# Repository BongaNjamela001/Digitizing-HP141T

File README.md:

# HP141T Spectrogram Display Project

This repository contains the complete set of files for the HP141T Spectrogram Display project, including hardware designs, simulations, software, and documentation. The project aims to visualize time-domain spectrogram data from the HP141T spectrum analyzer on a touchscreen LCD, replicating the CRT display with a green trace and grid.

## Repository Structure

The repository is organized into the following main folders:

- **PCBs/**: Hardware design files for the HP141T emulator and Signal Conditioning Subsystem.
- **Presentation/**: Materials for project presentations.
- **Report/**: Project report and associated LaTeX files.
- **Results/**: Output data and results from the project.
- **Simulations/**: Simulation files for circuit and signal analysis.
- **Software/**: Python scripts for data processing and GUI implementation.

### PCBs
This folder contains the PCB design files for the project, divided into two subdirectories:

- **HP141T_Emulator/**: KiCad project files and Gerber files for the HP141T emulator PCB.
- **Signal_Conditioning_Subsystem/**: KiCad project files and Gerber files for the Signal Conditioning Subsystem PCB.

### Presentation
This folder includes materials prepared for project presentations:

- **Poster/**: The project poster in PDF format.
- **Oral_Assessment/**: PowerPoint presentation (`.pptx`) for the oral assessment.

### Report
This folder contains the project report and its source files:

- **LaTeX/**: LaTeX source files for the project report.
- **Final_Report/**: Compiled PDF of the final project report.

### Results
This folder stores the output data and results generated during the project. It includes CSV files (e.g., `das-data_01.csv` to `das-data_64.csv`) with time and voltage measurements used for spectrogram visualization.

### Simulations
This folder contains simulation files for circuit and signal analysis:

- **LTSpice/**: LTSpice simulation files for circuit design validation.
- **MATLAB/**: MATLAB scripts and simulation files for signal processing and analysis.

### Software
This folder includes the software developed for the project:

- **DPS/**: Python scripts for data processing (e.g., `spectrogram_display_documented.py`).
- **GUIs/**: Python scripts for graphical user interfaces to interact with the spectrogram display.

## Usage

To explore the repository:

1. **Hardware**: Use KiCad to open the PCB design files in the `PCBs/` folder. Gerber files can be used for manufacturing.
2. **Simulations**: Run LTSpice simulations directly from the `.asc` files, or use MATLAB to execute the signal processing scripts.
3. **Software**: Navigate to the `Software/DPS/` folder to run the Python scripts. Ensure dependencies like `pandas`, `matplotlib`, and `tkinter` are installed. For example:
   ```bash
   python spectrogram_display_documented.py
   ```
4. **Documentation**: View the final report in `Report/Final_Report/` or compile the LaTeX source in `Report/LaTeX/`.

## License

This project is licensed under the MIT License. See the `LICENSE` file for details (to be added).

## Contributing

Contributions are welcome! Please submit a pull request or open an issue to discuss improvements or bug fixes.

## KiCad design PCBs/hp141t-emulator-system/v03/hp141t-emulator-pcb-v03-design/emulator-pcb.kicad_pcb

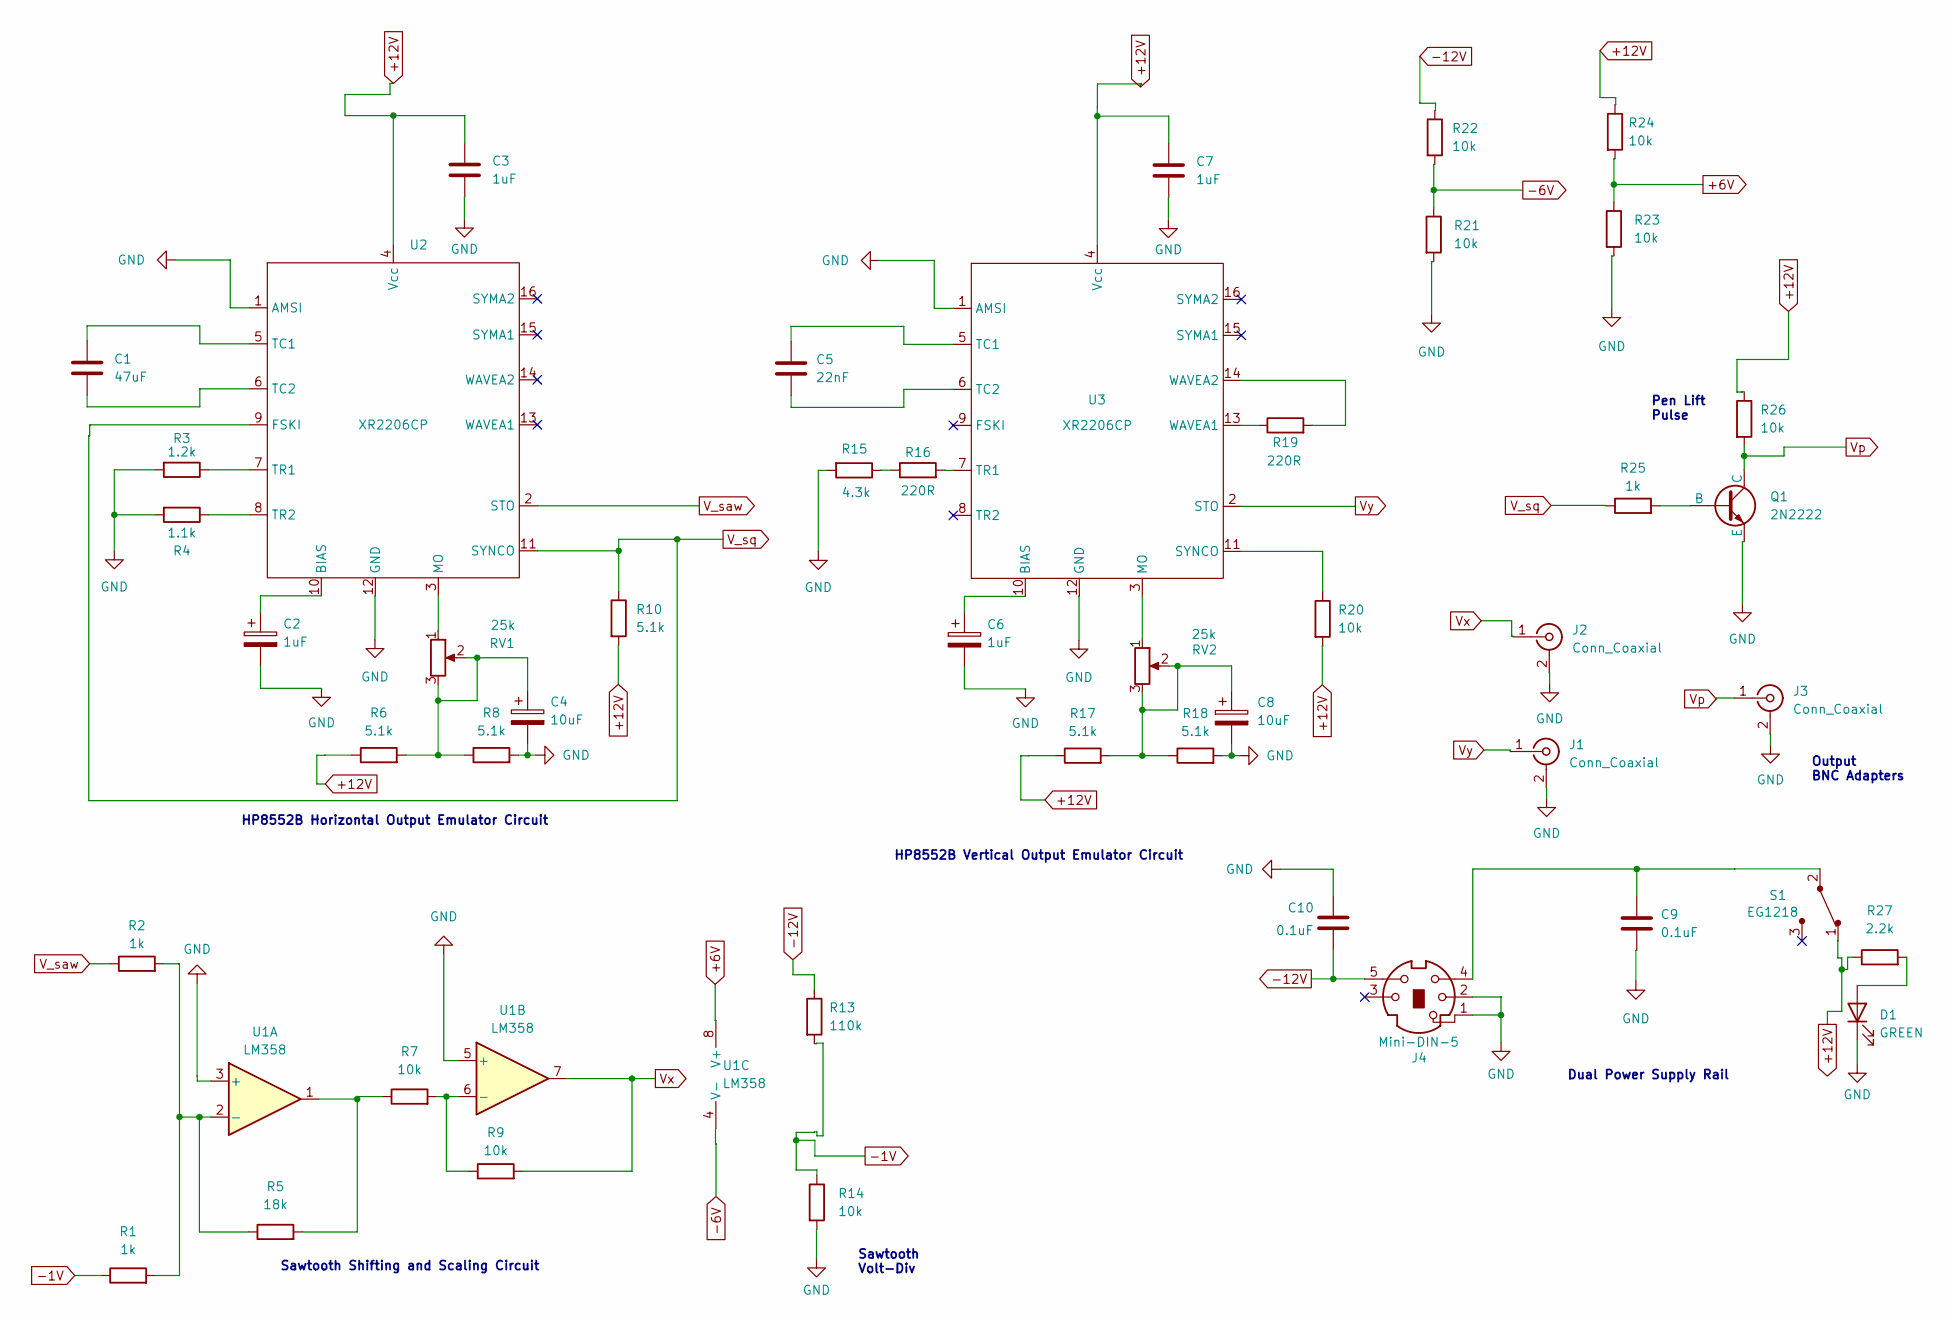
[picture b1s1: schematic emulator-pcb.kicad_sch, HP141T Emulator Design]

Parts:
C1: 47uF; C_Axial_L12.0mm_D6.5mm_P20.00mm_Horizontal
C2, C6: 1uF; CP_Radial_D6.3mm_P2.50mm
C3, C7: 1uF; C_Axial_L3.8mm_D2.6mm_P7.50mm_Horizontal
C4, C8: 10uF; CP_Radial_D4.0mm_P1.50mm
C5: 22nF; C_Axial_L3.8mm_D2.6mm_P7.50mm_Horizontal
C9, C10: 0.1uF; C_Axial_L3.8mm_D2.6mm_P7.50mm_Horizontal
D1: GREEN; LED_D5.0mm
J1, J2, J3: Conn_Coaxial; BNC_Amphenol_B6252HB-NPP3G-50_Horizontal
J4: Mini-DIN-5; PinSocket_DIN41524_1x05_P2.54mm_Vertical
Q1: 2N2222; TO-92_Inline
R1, R2, R25: 1k; R_Axial_DIN0207_L6.3mm_D2.5mm_P7.62mm_Horizontal
R3: 1.2k; R_Axial_DIN0207_L6.3mm_D2.5mm_P7.62mm_Horizontal
R4: 1.1k; R_Axial_DIN0207_L6.3mm_D2.5mm_P7.62mm_Horizontal
R5: 18k; R_Axial_DIN0207_L6.3mm_D2.5mm_P7.62mm_Horizontal
R6, R8, R10, R17, R18: 5.1k; R_Axial_DIN0207_L6.3mm_D2.5mm_P7.62mm_Horizontal
R7, R9, R14, R20, R21, R22, R23, R24, R26: 10k; R_Axial_DIN0207_L6.3mm_D2.5mm_P7.62mm_Horizontal
R13: 110k; R_Axial_DIN0207_L6.3mm_D2.5mm_P7.62mm_Horizontal
R15: 4.3k; R_Axial_DIN0207_L6.3mm_D2.5mm_P7.62mm_Horizontal
R16, R19: 220R; R_Axial_DIN0207_L6.3mm_D2.5mm_P7.62mm_Horizontal
R27: 2.2k; R_Axial_DIN0207_L6.3mm_D2.5mm_P7.62mm_Horizontal
RV1, RV2: 25k; BOURNS-3362P_pot
S1: EG1218; Switch_Slide_11.6x4mm_EG1218; MPN EG1218; Digi-Key_PN EG1903-ND
U1: LM358; DIP-8_W7.62mm_Socket
U2, U3: XR2206CP; Socket_DIP-16_7.62mm_Conn

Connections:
+6V: R23.1, R24.2, U1.8 (V+)
+12V: C3.1, C7.1, R6.1, R10.2, R17.1, R20.2, R24.1, R26.1, R27.1, S1.1, U2.4 (Vcc), U3.4 (Vcc)
-1V: R1.1, R13.2, R14.1
-6V: R21.1, R22.2, U1.4 (V-)
-12V: C10.2, J4.5, R13.1, R22.1
GND: C2.2, C3.2, C4.2, C6.2, C7.2, C8.2, C9.2, C10.1, D1.1 (K), J1.2 (Ext), J2.2 (Ext), J3.2 (Ext), J4.1, J4.2, Q1.3 (E), R3.2, R4.2, R8.2, R14.2, R15.2, R18.2, R21.2, R23.2, U1.3 (+), U1.5 (+), U2.1 (AMSI), U2.12 (GND), U3.1 (AMSI), U3.12 (GND); also elsewhere on the board
unnamed: C4.1, R6.2, R8.1, RV1.2, RV1.3
unnamed: C8.1, R17.2, R18.1, RV2.2, RV2.3
unnamed: C9.1, J4.4, S1.2
unnamed: D1.2 (A), R27.2
unnamed: Q1.2 (B), R25.2
unnamed: R5.2, R7.1, U1.1
unnamed: R15.1, R16.1
unnamed: R1.2, R2.2, R5.1, U1.2 (-)
unnamed: R7.2, R9.1, U1.6 (-)
unnamed: C2.1, U2.10 (BIAS)
unnamed: RV1.1, U2.3 (MO)
unnamed: C1.1, U2.5 (TC1)
unnamed: C1.2, U2.6 (TC2)
unnamed: R3.1, U2.7 (TR1)
unnamed: R4.1, U2.8 (TR2)
unnamed: C6.1, U3.10 (BIAS)
unnamed: RV2.1, U3.3 (MO)
unnamed: R20.1, U3.11 (SYNCO)
unnamed: C5.1, U3.5 (TC1)
unnamed: C5.2, U3.6 (TC2)
unnamed: R16.2, U3.7 (TR1)
unnamed: R19.1, U3.13 (WAVEA1)
unnamed: R19.2, U3.14 (WAVEA2)
V_saw: R2.1, U2.2 (STO)
V_sq: R10.1, R25.1, U2.9 (FSKI), U2.11 (SYNCO)
Vp: J3.1 (In), Q1.1 (C), R26.2
Vx: J2.1 (In), R9.2, U1.7
Vy: J1.1 (In), U3.2 (STO)

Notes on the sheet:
Dual Power Supply Rail
Sawtooth Shifting and Scaling Circuit
Output BNC Adapters
Pen Lift Pulse
HP8552B Horizontal Output Emulator Circuit
Sawtooth Volt-Div
HP8552B Vertical Output Emulator Circuit

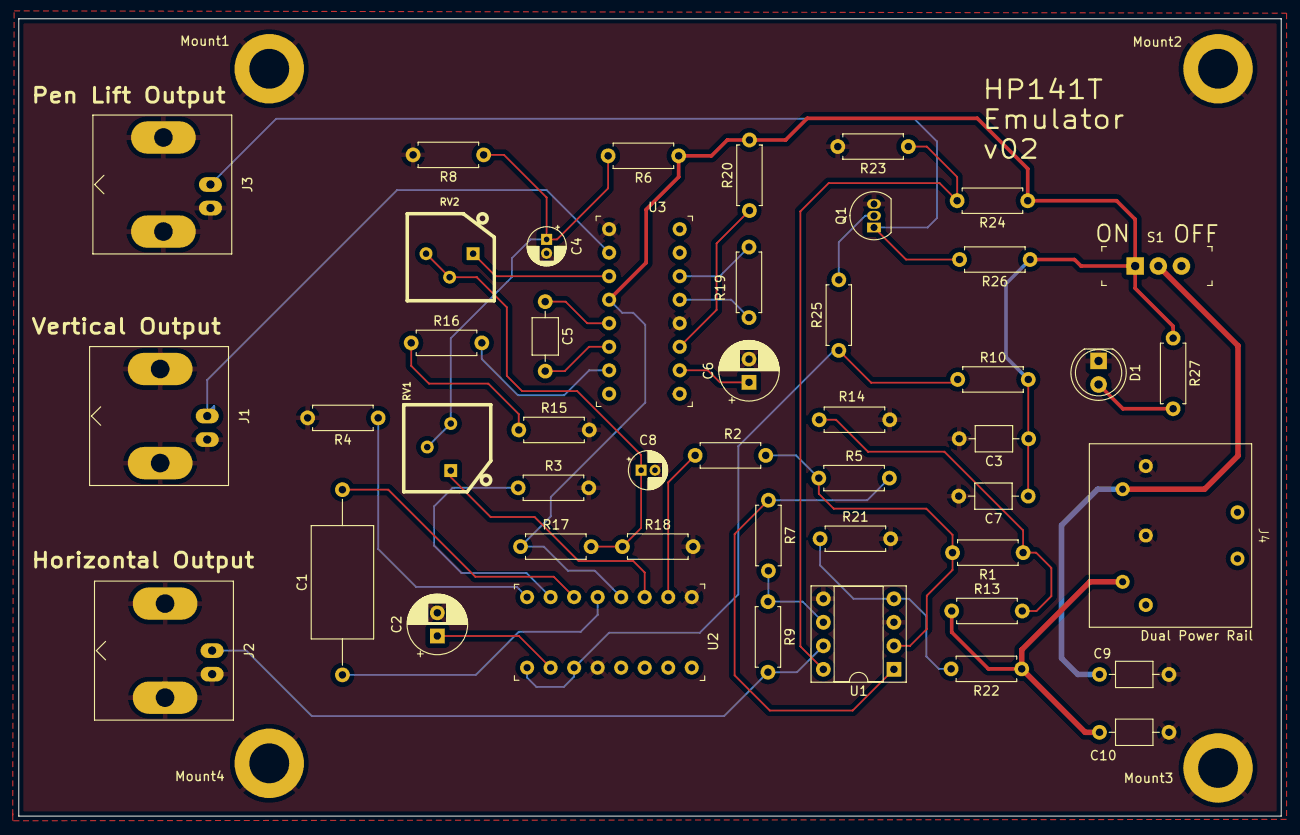
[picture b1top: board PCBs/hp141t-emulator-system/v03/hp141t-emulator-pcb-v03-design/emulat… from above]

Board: 2 copper layers, 136.3 x 86.1 mm, 51 parts (0 on the bottom side), 34 nets.

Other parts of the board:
Mount1, Mount2, Mount3, Mount4: MountingHole_4.3mm_M4_DIN965_Pad

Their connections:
GND: Mount1.1, Mount2.1, Mount3.1, Mount4.1; also elsewhere on the board

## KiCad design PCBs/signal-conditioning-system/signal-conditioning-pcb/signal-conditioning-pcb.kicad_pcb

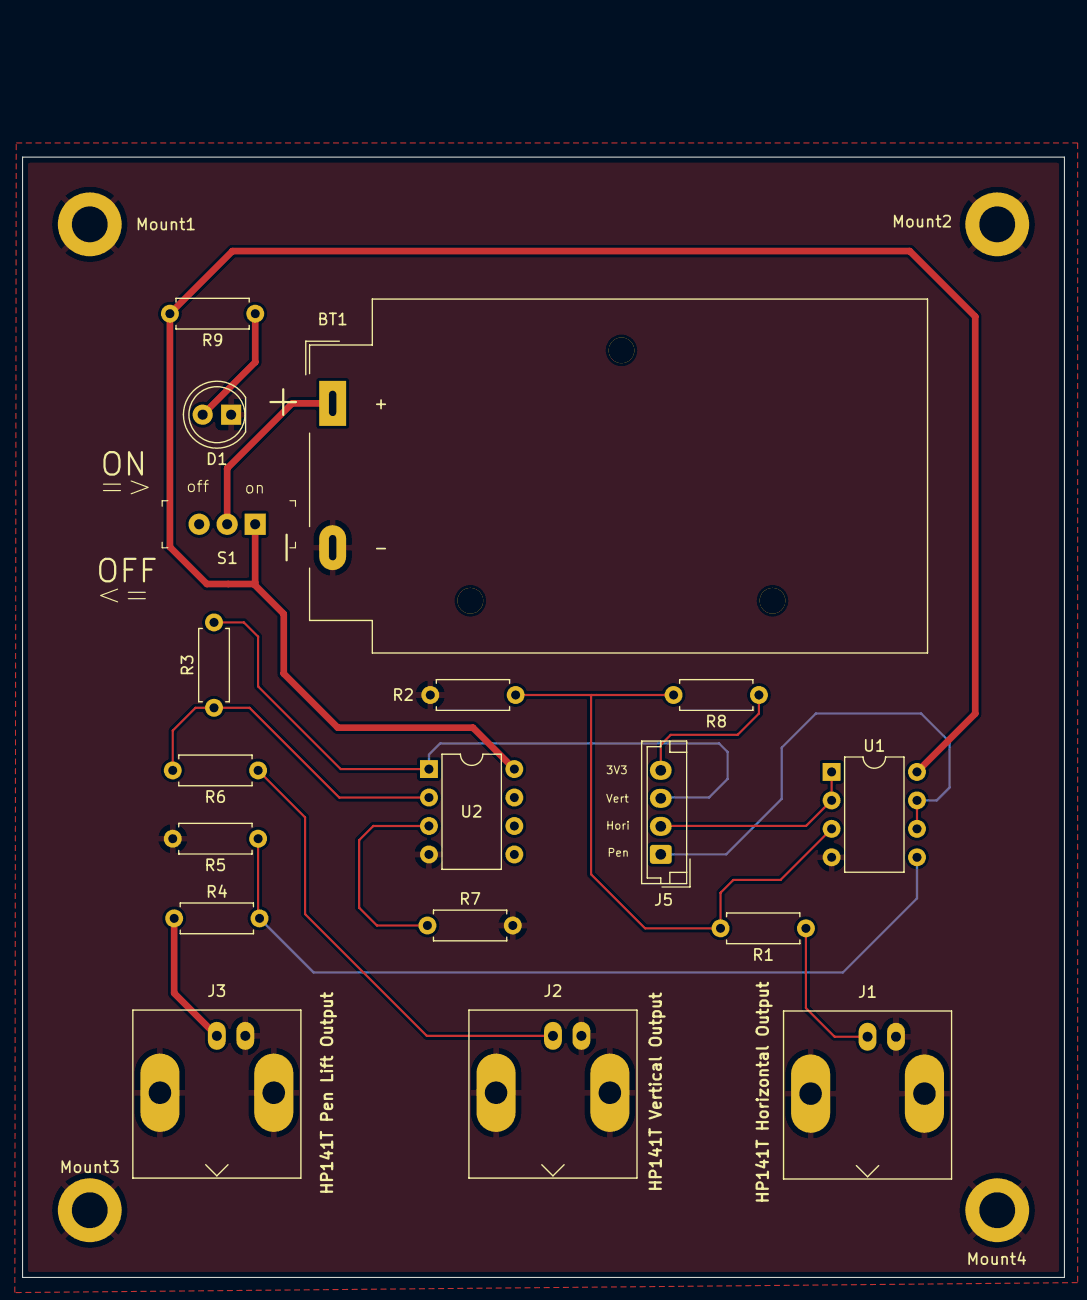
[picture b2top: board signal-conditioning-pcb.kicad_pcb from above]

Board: 2 copper layers, 93.0 x 112.0 mm, 22 parts (0 on the bottom side), 15 nets.

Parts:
BT1: 9V; BatteryHolder_MPD_BA9VPC_1xPP3
D1: Green; LED_D5.0mm
J1, J2, J3: Conn_Coaxial; BNC_Amphenol_B6252HB-NPP3G-50_Horizontal
J5: Conn_01x04_Pin; JST_EH_B4B-EH-A_1x04_P2.50mm_Vertical
Mount1, Mount2, Mount3, Mount4: MountingHole_3.2mm_M3_ISO7380_Pad
R1: 100k; R_Axial_DIN0207_L6.3mm_D2.5mm_P7.62mm_Horizontal
R2: 200k; R_Axial_DIN0207_L6.3mm_D2.5mm_P7.62mm_Horizontal
R3, R5: 10k; R_Axial_DIN0207_L6.3mm_D2.5mm_P7.62mm_Horizontal
R4: 47k; R_Axial_DIN0207_L6.3mm_D2.5mm_P7.62mm_Horizontal
R6: 2.7k; R_Axial_DIN0207_L6.3mm_D2.5mm_P7.62mm_Horizontal
R7: 2.2k; R_Axial_DIN0207_L6.3mm_D2.5mm_P7.62mm_Horizontal
R8: 68k; R_Axial_DIN0207_L6.3mm_D2.5mm_P7.62mm_Horizontal
R9: 470R; R_Axial_DIN0207_L6.3mm_D2.5mm_P7.62mm_Horizontal
S1: EG1218; Switch_Slide_11.6x4mm_EG1218
U1, U2: LM358; DIP-8_W7.62mm

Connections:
3V3: J5.4, R8.1
+9V: R9.2, S1.1, U1.8 (V+), U2.8 (V+)
GND: BT1.2 (-), D1.1 (K), J1.2 (Ext), J2.2 (Ext), J3.2 (Ext), Mount1.1, Mount2.1, Mount3.1, Mount4.1, R2.2, R5.2, R7.2, U1.4 (V-), U2.4 (V-)
unnamed: BT1.1 (+), S1.2
unnamed: D1.2 (A), R9.1
unnamed: R1.2, R2.1, R8.2, U1.3 (+)
unnamed: R4.2, R5.1, U1.5 (+)
unnamed: R7.1, U2.3 (+)
unnamed: R3.1, R6.2, U2.2 (-)
V_hin: J1.1 (In), R1.1
V_hout: J5.2, U1.1, U1.2 (-)
V_penin: J3.1 (In), R4.1
V_penout: J5.1, U1.6 (-), U1.7
V_vin: J2.1 (In), R6.1
V_vout: J5.3, R3.2, U2.1

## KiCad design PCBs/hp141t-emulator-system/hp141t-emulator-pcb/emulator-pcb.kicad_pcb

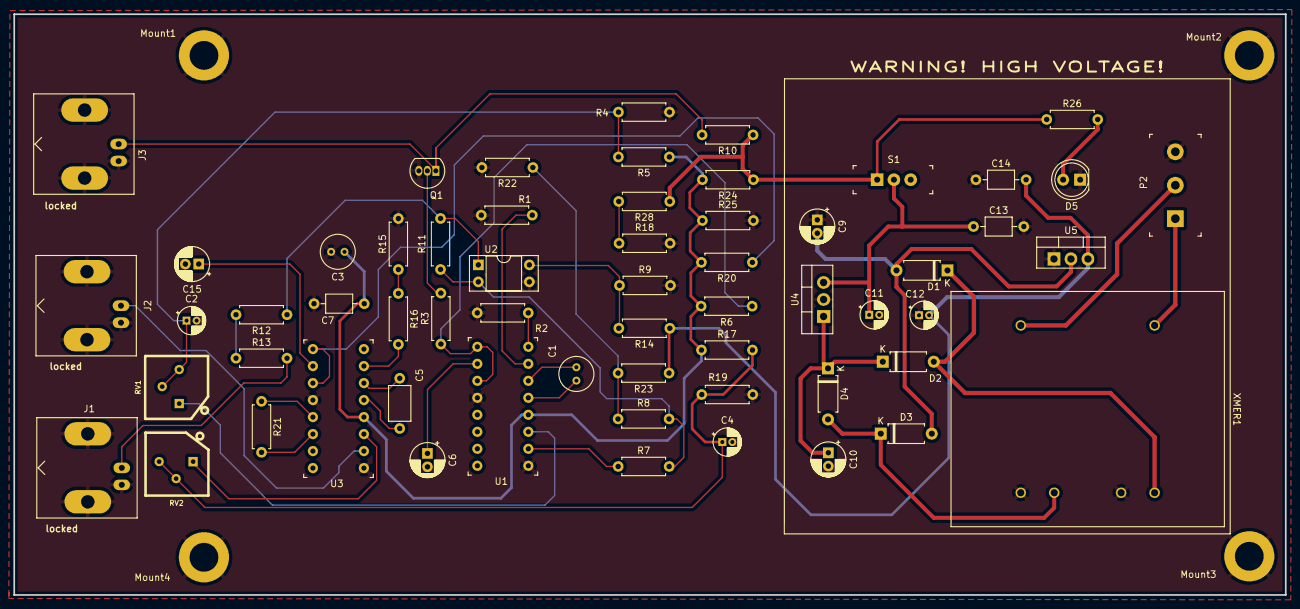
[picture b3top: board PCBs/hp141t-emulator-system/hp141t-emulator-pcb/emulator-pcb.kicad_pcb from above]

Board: 2 copper layers, 190.0 x 86.8 mm, 64 parts (0 on the bottom side), 41 nets.

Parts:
C1: 47uF; C_Radial_D5.0mm_H5.0mm_P2.00mm
C2, C4, C11, C12: 10uF; CP_Radial_D4.0mm_P1.50mm
C3: 1uF; C_Radial_D5.0mm_H5.0mm_P2.00mm
C5: 22nF; C_Axial_L5.1mm_D3.1mm_P7.50mm_Horizontal
C6, C15: 1uF; CP_Radial_D5.0mm_P2.00mm
C7: 1uF; C_Axial_L3.8mm_D2.6mm_P7.50mm_Horizontal
C9, C10: 1mF; CP_Radial_D5.0mm_P2.00mm
C13, C14: 0.1uF; C_Axial_L3.8mm_D2.6mm_P7.50mm_Horizontal
D1, D2, D3, D4: 1N4007; D_A-405_P7.62mm_Horizontal
D5: GREEN; LED_D5.0mm
J1, J2, J3: Conn_Coaxial; BNC_Amphenol_B6252HB-NPP3G-50_Horizontal
Mount1, Mount2, Mount3, Mount4: MountingHole_4.3mm_M4_DIN965_Pad
P2: Conn_WallPlug_Earth; Term_Block_1x3_P5mm
Q1: 2N2222; TO-92_Inline
R1: 1.5k; R_Axial_DIN0207_L6.3mm_D2.5mm_P7.62mm_Horizontal
R2: 1.2k; R_Axial_DIN0207_L6.3mm_D2.5mm_P7.62mm_Horizontal
R3, R7, R8: 1k; R_Axial_DIN0207_L6.3mm_D2.5mm_P7.62mm_Horizontal
R4, R5, R6, R17, R19: 5.1k; R_Axial_DIN0207_L6.3mm_D2.5mm_P7.62mm_Horizontal
R9, R10, R12, R13, R14, R18, R20, R22, R25, R28: 10k; R_Axial_DIN0207_L6.3mm_D2.5mm_P7.62mm_Horizontal
R11: 18k; R_Axial_DIN0207_L6.3mm_D2.5mm_P7.62mm_Horizontal
R15: 4.3k; R_Axial_DIN0207_L6.3mm_D2.5mm_P7.62mm_Horizontal
R16, R21: 220R; R_Axial_DIN0207_L6.3mm_D2.5mm_P7.62mm_Horizontal
R23: 110k; R_Axial_DIN0207_L6.3mm_D2.5mm_P7.62mm_Horizontal
R24: 3.3k; R_Axial_DIN0207_L6.3mm_D2.5mm_P7.62mm_Horizontal
R26: 100k; R_Axial_DIN0207_L6.3mm_D2.5mm_P7.62mm_Horizontal
RV1, RV2: 25k; BOURNS-3362P_pot
S1: EG1218; Switch_Slide_11.6x4mm_EG1218
U1, U3: XR2206CP; Socket_DIP-16_7.62mm_Conn
U2: LM358; DIP-4_W7.62mm_Socket
U4: LM7812_TO220; TO-220-3_Vertical
U5: LM7912_TO220; TO-220-3_Vertical
XMER1: 44202; 44202_MYR

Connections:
12V1: C11.1, C13.1, S1.2, U4.3 (VO)
+6V: R18.1, R28.2
+9V: C3.1, C7.1, R5.1, R6.2, R17.1, R20.2, R24.2, R25.1, U1.4 (Vcc), U3.4 (Vcc)
+12V: R10.1, R24.1, R26.1, R28.1, S1.1
-1V: R8.1, R22.1, R23.2
-6V: R9.1, R14.2, U2.4 (V-)
-12V: C12.2, C14.2, R14.1, R23.1, U5.3 (VO)
GND: C2.2, C3.2, C4.2, C6.2, C7.2, C9.1, C10.2, C11.2, C12.1, C13.2, C14.1, C15.2, D5.1 (K), J1.2 (Ext), J2.2 (Ext), J3.2 (Ext), Mount1.1, Mount2.1, Mount3.1, Mount4.1, P2.3 (EARTH), Q1.3 (E), R1.2, R2.2, R4.2, R9.2, R15.2, R18.2, R19.2, R22.2, R25.2, U1.1 (AMSI), U1.12 (GND), U2.3 (+), U3.1 (AMSI), U3.12 (GND), U4.2 (GND), U5.1 (GND), XMER1.6, XMER1.9
unnamed: C2.1, R4.1, R5.2, RV1.2, RV1.3
unnamed: C4.1, R17.2, R19.1, RV2.2, RV2.3
unnamed: C9.2, D1.2 (A), D3.2 (A), U5.2 (VI)
unnamed: D1.1 (K), D2.2 (A), XMER1.10
unnamed: C10.1, D2.1 (K), D4.1 (K), U4.1 (VI)
unnamed: D3.1 (K), D4.2 (A), XMER1.7
unnamed: D5.2 (A), R26.2
unnamed: P2.2 (AC_N), XMER1.5
unnamed: P2.1 (AC_P), XMER1.1
unnamed: Q1.2 (B), R3.2
unnamed: R11.2, R12.1, U2.1
unnamed: R15.1, R16.1
unnamed: C6.1, U1.10 (BIAS)
unnamed: RV1.1, U1.3 (MO)
unnamed: C1.1, U1.5 (TC1)
unnamed: C1.2, U1.6 (TC2)
unnamed: R1.1, U1.7 (TR1)
unnamed: R2.1, U1.8 (TR2)
unnamed: R7.2, R8.2, R11.1, U2.2 (-)
unnamed: R12.2, R13.1
unnamed: C15.1, U3.10 (BIAS)
unnamed: R20.1, U3.9 (FSKI), U3.11 (SYNCO)
unnamed: RV2.1, U3.3 (MO)
unnamed: C5.1, U3.5 (TC1)
unnamed: C5.2, U3.6 (TC2)
unnamed: R16.2, U3.7 (TR1)
unnamed: R21.1, U3.13 (WAVEA1)
unnamed: R21.2, U3.14 (WAVEA2)
V_saw: R7.1, U1.2 (STO)
V_sq: R3.1, R6.1, U1.9 (FSKI), U1.11 (SYNCO)
Vp: J3.1 (In), Q1.1 (C), R10.2
Vx: J1.1 (In), R13.2
Vy: J2.1 (In), U3.2 (STO)

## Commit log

2025-03-12 Added report as backup and for version control.
2025-03-13 Complete methodology overview and start of requirements review.
2025-03-15 Started comparison of 141T to modern SAs in requirements review.
2025-03-17 Completed requirements review and system block diagram.
2025-04-01 Completed history section in literature review.
2025-04-04 Completed Signal Conditioning PCB design.
2025-04-04 Added GND mounting holes to SigConditioningCirc
2025-04-08 Completed the HP141T Emulator Board
2025-04-10 Updated Emulator PCB from v01 to v02. Power supply change.
2025-04-10 Removed voltage divider. Added 0.1uF power capacitors.
2025-04-22 Updated hp141t emulator. Removed +12V to +9V divider
2025-04-25 Uploaded simulation files.
2025-04-25 Uploaded MATLAB ADC sim files and results.
2025-04-25 Uploaded MATLAB ADC simulation for STM32H723ZG
2025-04-27 Expanded on specifications report.
2025-04-28 Completed report HP141T subsystem design specifications.
2025-04-29 Updated the Signal Conditioning Subsystem specifications in report.
2025-05-09 Proceeding to complete the methodology.
2025-05-10 Updated specifications of the SCS.
2025-05-11 Completed the adc.c module in the Software directory.
2025-05-21 Completed DAS design and collected some results.
2025-05-23 Updated report. Documented test procedures.
2025-05-29 Complete with presentation slides and poster.
